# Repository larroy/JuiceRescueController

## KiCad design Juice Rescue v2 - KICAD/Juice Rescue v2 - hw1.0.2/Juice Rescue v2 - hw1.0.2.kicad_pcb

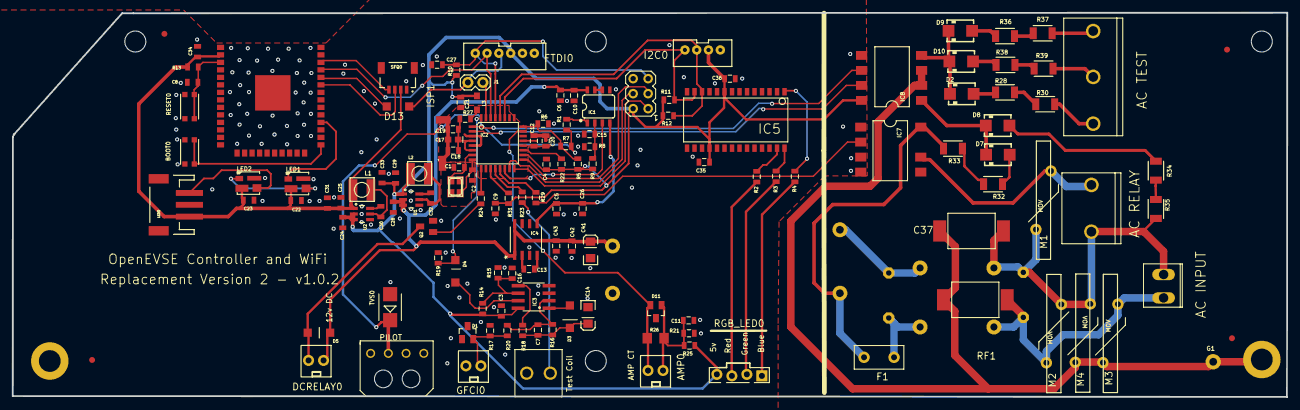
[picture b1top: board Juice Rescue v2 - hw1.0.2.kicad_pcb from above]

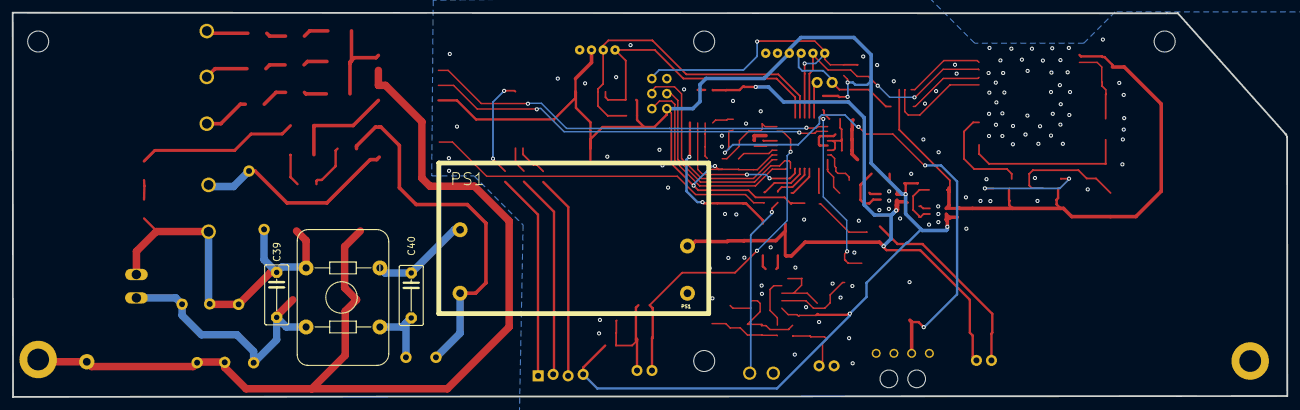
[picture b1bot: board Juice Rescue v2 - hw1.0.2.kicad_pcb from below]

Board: 2 copper layers, 215.8 x 65.1 mm, 148 parts (4 on the bottom side), 90 nets.

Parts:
AC0: 2POS3.96MM; 2POS3.66MM
AC_TEST0: AMPAC3P; ACAMP3P
AMP0: AMP_CT; MOLEX_2
BOOT0: KMR2; BTN_KMR2_4.6X2.8
C1, C2: 22pf; 0805
C3, C4, C7, C9, C10, C11, C12, C15, C16, C21, C26, C27, C35, C36, C43: .1uf; 0805
C5, C6, C13: 10uf; 0805
C8: 1.0uF; 0805_510
C14, C41: 10uf; EIA3216
C17: 10uF; 0603-POLAR
C18: 1uF; 0805
C19: 0.1uF; 0805
C20, C42: 1uf; 0805
C22, C23, C34: .1uf; 0805_510
C24, C28: 10uf; 0805_510
C25, C29, C31, C33: 22; 0805_510
C30, C32: 100nf; 0805_510
C37: 1000pf; DK1E3EA
C39, C40: 10000pf; C7.5B4_116
CMC0: RN214-0.3-02-47M
D1: AZ23C5V6-7-F; SOT23
D2, D7, D8, D9, D10: 1N4004; SMA
D3, D4, D5, D13: 1N4148; SOD123
D11: AZ23C2V7-7-F; SOT23
DCRELAY0: AMP_CT; MOLEX_2
F1: BEL1.6AFUSE; BELFUSE1A
FID1, FID2, FID3, FID4: FIDUCIAL1X2.5; FIDUCIAL-1X2.5
FTDI0: JST6
G1: M01PTH; 1X01
GFCI0: AMP_CT; MOLEX_2
I2C0: JST-4-PTH-VERT
IC1: LMV358; SO08_520
IC2: ATMEGA328P-AU; TQFP32-08
IC3: LM358; SO08
IC4: TC1044S; SO-8
IC5: MCP23017SO; SO28W
IC7: AQH2223; SIL8
IC8: HCPL-2731S; SIL8-2
ISP1: ISP1; AVRISP
J1: 1X02_513
L1, L2: 3.3uh; MICROBUILDER_INDUCTOR_5X5MM_NR5040_NOTHERMALS
L3: BLM21PG331SN1D; INDC2012X87
LED0: 3-PIN SMD; JST-3-SMD
LED1, LED2: WS2812B3535; LED3535
M1, M2, M3, M4: MOV
PS1: IRM-10-5
Q1: 16000; NX3225
Q2: 2222A; SOT23
R1: 820; 0805
R2, R3, R4: 220; 0805
R5: 56k; 0805
R6, R8, R9, R14, R16, R21, R25: 100k; 0805
R7: 200k; 0805
R10, R19, R22, R31: 10k; 0805
R11, R12: 4.7k; 0805
R13: 10k; 0805_532
R15: 20k; 0805
R17: 422; 0805
R18: 100; 0805
R20: 1k; 0805
R23, R24, R29: 330; 0805
R26: 22; R1206
R27: 2.0; 0805
R28, R30, R32, R33, R34, R35, R36, R37, R38, R39: 180k; 1210
RESET0: KMR2; BTN_KMR2_4.6X2.8
RF1: 1000pf; DK1E3EA
RGB_LED0: GFCI_CT; GFCI_4
SFQ0: JST04_1MM_RA
SH1, SH2: SHORT-HT5; SHORT_TOP-50
TEST_COIL0: 2X4MM
TVS0: P6SMB16CA; SMB
U1, U2: AP63203; SOT23-6
U$3, U$9: HOLE
U$8: AMPAC
U$25: 4X3MM_MOLEX
UNK_HOLE_0: dummyfp0
UNK_HOLE_1: dummyfp1
UNK_HOLE_2: dummyfp2
UNK_HOLE_3: dummyfp3
X2: ESP32-WROOM-32; WROOM32_SKINNY

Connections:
3.3V: C22.1, C23.1, C25.1, C31.1, C34.1, L1.P$2, LED0.1, LED1.2, LED2.2, R13.1, SFQ0.2, U2.1, X2.2
+5V: C3.1, C4.1, C9.1, C21.1, C24.1, C29.1, C33.1, C35.1, C36.1, FTDI0.3, I2C0.2, IC2.18, IC3.8, IC5.9, IC5.18, IC8.P$8, ISP1.2, L2.P$2, L3.1, R5.2, R9.1, R10.2, R11.2, R12.2, R14.1, R22.2, R25.1, R31.2, RGB_LED0.4, U1.1, U2.2, U2.3
+12V: C6.2, C10.1, C28.1, C41.A, C42.1, C43.2, D5.C, DCRELAY0.2, IC1.8, IC4.1, IC4.8, PS1.V+, U1.2, U1.3
-12V1: C5.1, C26.2, IC1.4, IC4.5
ACL: C40.2, CMC0.P$1, F1.OUT
ACLFUSE: F1.IN, IC7.P$8, PS1.AC/L, R33.2
ACLIN: AC0.P$6, C39.2, CMC0.P$2, M2.P$2, M3.P$2, RF1.P$2
ACN: C40.1, CMC0.P$3, PS1.AC/N
ACNIN: AC0.P$5, C37.P$2, C39.1, CMC0.P$4, M1.P$1, M2.P$1, M4.P$2, R35.2, U$8.P$1
ACRELAY: IC7.P$6, M1.P$2, U$8.P$2
ACTEST1: AC_TEST0.P$3, R37.2
ACTEST2: AC_TEST0.P$2, R39.2
ACTEST3: AC_TEST0.P$1, R30.2
AC_RELAY_1: IC2.13, R29.2
ADC6: IC2.19, R22.1
AMP_READ: AMP0.1, D11.2, IC2.23, R26.2
AREF: C12.1, C20.1, IC2.20
BLUE: IC5.1, R4.2
DAMP: L3.2, R27.2
DC_RELAY_1: IC2.9, R24.2
DC_RELAY_1_O: D5.A, DCRELAY0.1, Q2.3
DC_RELAY_1_T: Q2.1, R24.1
ESPRESET: C8.1, R13.2, RESET0.B, RESET0.B', X2.3
ESPSCL: SFQ0.4, X2.36
ESPSDA: SFQ0.3, X2.33
GFCI_INT: D4.C, IC2.32, R19.1
GFCI_TEST: IC2.12, R23.1
GFI_TEST_O: R23.2, TEST_COIL0.P$1
GMI_LINE: IC2.2, IC8.P$7
GND: BOOT0.A, BOOT0.A', C3.2, C4.2, C5.2, C6.1, C8.2, C9.2, C10.2, C11.2, C14.C, C15.1, C16.1, C22.2, C23.2, C24.2, C25.2, C26.1, C27.1, C28.2, C29.2, C31.2, C33.2, C34.2, C35.2, C36.2, C41.C, C42.2, C43.1, D1.1, FTDI0.1, GFCI0.1, I2C0.1, IC1.5, IC3.3, IC3.4, IC4.3, IC5.10, IC5.15, IC5.16, IC5.17, IC7.P$1, IC7.P$3, IC7.P$4, IC8.P$5, ISP1.6, LED0.2, LED1.4, LED2.4, PS1.V-, Q2.2, R6.2, R8.1, R15.2, R17.1, R19.2, R21.2, RESET0.A, RESET0.A', SFQ0.1, SH1.2, TEST_COIL0.P$2, TVS0.A, U1.4, U2.4, U$9.P$1, X2.1, X2.15, X2.38, X2.P$1
GPIO0: BOOT0.B, BOOT0.B', X2.25
GREEN: IC5.28, R3.2
LED: LED1.1, X2.28
MISO: IC2.16, ISP1.1
MOSI: IC2.15, ISP1.4
unnamed: D2.C, D9.C, D10.C, IC8.P$4
unnamed: D7.C, D8.C, IC8.P$1
unnamed: C1.2, IC2.7, Q1.2
unnamed: C2.1, IC2.8, Q1.4
unnamed: D7.A, R32.1
unnamed: AMP0.2, C11.1, D11.1, R21.1, R25.2, R26.1
unnamed: C7.1, IC3.2, R16.2, R20.1
unnamed: D8.A, R34.1
unnamed: C15.2, IC1.2, R8.2, R9.2
unnamed: IC1.1, R1.2
unnamed: IC2.11, R31.1
unnamed: R32.2, R33.1
unnamed: IC1.6, IC1.7
unnamed: C32.1, U1.6
unnamed: C32.2, L2.P$1, U1.5
unnamed: R34.2, R35.1
unnamed: IC7.P$2, R29.1
unnamed: C13.2, IC4.2
unnamed: D3.A, IC3.1
unnamed: R36.2, R37.1
unnamed: C7.2, C14.A, D3.C, R16.1, R18.2
unnamed: C16.2, IC3.6, R14.2, R15.1
unnamed: D4.A, IC3.7
unnamed: IC3.5, R18.1
unnamed: C13.1, IC4.4
unnamed: R38.2, R39.1
unnamed: D9.A, R36.1
unnamed: D10.A, R38.1
unnamed: R3.1, RGB_LED0.2
unnamed: R2.1, RGB_LED0.3
unnamed: LED1.3, LED2.1
unnamed: C30.1, U2.6
unnamed: C30.2, L1.P$1, U2.5
unnamed: R4.1, RGB_LED0.1
unnamed: IC2.31, J1.2
unnamed: D2.A, R28.1
unnamed: R28.2, R30.1
unnamed: D1.2, GFCI0.2, R17.2, R20.2
PE: C37.P$1, G1.1, IC8.P$2, IC8.P$3, M3.P$1, M4.P$1, RF1.P$1, U$3.P$1
PILOT: R1.1, R7.2, TVS0.C, U$25.P$3
PILOTREAD: IC2.24, R5.1, R6.1, R7.1
PIX: LED0.3, LED2.3
PWM: IC1.3, IC2.14
RED: IC5.27, R2.2
RESET: C27.2, FTDI0.6, IC2.29, ISP1.5, R10.1
RX-I: FTDI0.5, IC2.30, X2.35
RXD0: D13.A, X2.34
SCK: IC2.17, ISP1.3
SCL: I2C0.3, IC2.28, IC5.12, R12.1
SDA: I2C0.4, IC2.27, IC5.13, R11.1
TX: D13.C, FTDI0.4, J1.1
UGND: C12.2, C17.-, C18.1, C19.1, C20.2, C21.2, IC2.3, IC2.5, IC2.21, SH1.1, SH2.2
VCC: C17.+, C18.2, C19.2, IC2.4, IC2.6, R27.1
WELD_DETECT: IC2.1, IC8.P$6
XGND: C1.1, C2.2, Q1.1, Q1.3, SH2.1

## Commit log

2026-03-06 Convert to Kicad 9.0
2026-03-07 modif
2026-03-07 level shifter and temp
2026-03-07 ESP32 update.
2026-03-07 minor update.
2026-03-08 Hw changes.
2026-05-14 cosmetic
